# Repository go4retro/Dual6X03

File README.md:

# Dual 6X03 Adapter Schematic and Printed Circuit Board v1.0
This PCB will allow the use of two different 6X03 variants in a 6803-based system.  Only one CPU can be active at any time, and the CPU must be selected before boot.

## Theory
The 6X03 device can operate in modes 6801 configuration mode 2 or 3 only.  Essentially, Expanded Multiplexed mode with or without ROM.  At this moment, it is unclear how many of the 6X03 pins are tristated during RESET, so I took the safe approach of placing all known output lines (Address, Data, AS, E, R/W), and a few lines known to be outputs on the TANDY MC-10 (the first target of this PCB) to ensure operation.  If testing proves all lines to be in tristate or read state during RESET, I will simplify the schematic.

## License
Copyright (C) 2018  Jim Brain, RETRO Innovations

These files are free designs; you can redistribute them and/or modify
them under the terms of the Creative Commons Attribution-ShareAlike 
4.0 International License.

You should have received a copy of the license along with this
work. If not, see <http://creativecommons.org/licenses/by-sa/4.0/>.

These files are distributed in the hope that they will be useful,
but WITHOUT ANY WARRANTY; without even the implied warranty of
MERCHANTABILITY or FITNESS FOR A PARTICULAR PURPOSE.  See the
license for more details.

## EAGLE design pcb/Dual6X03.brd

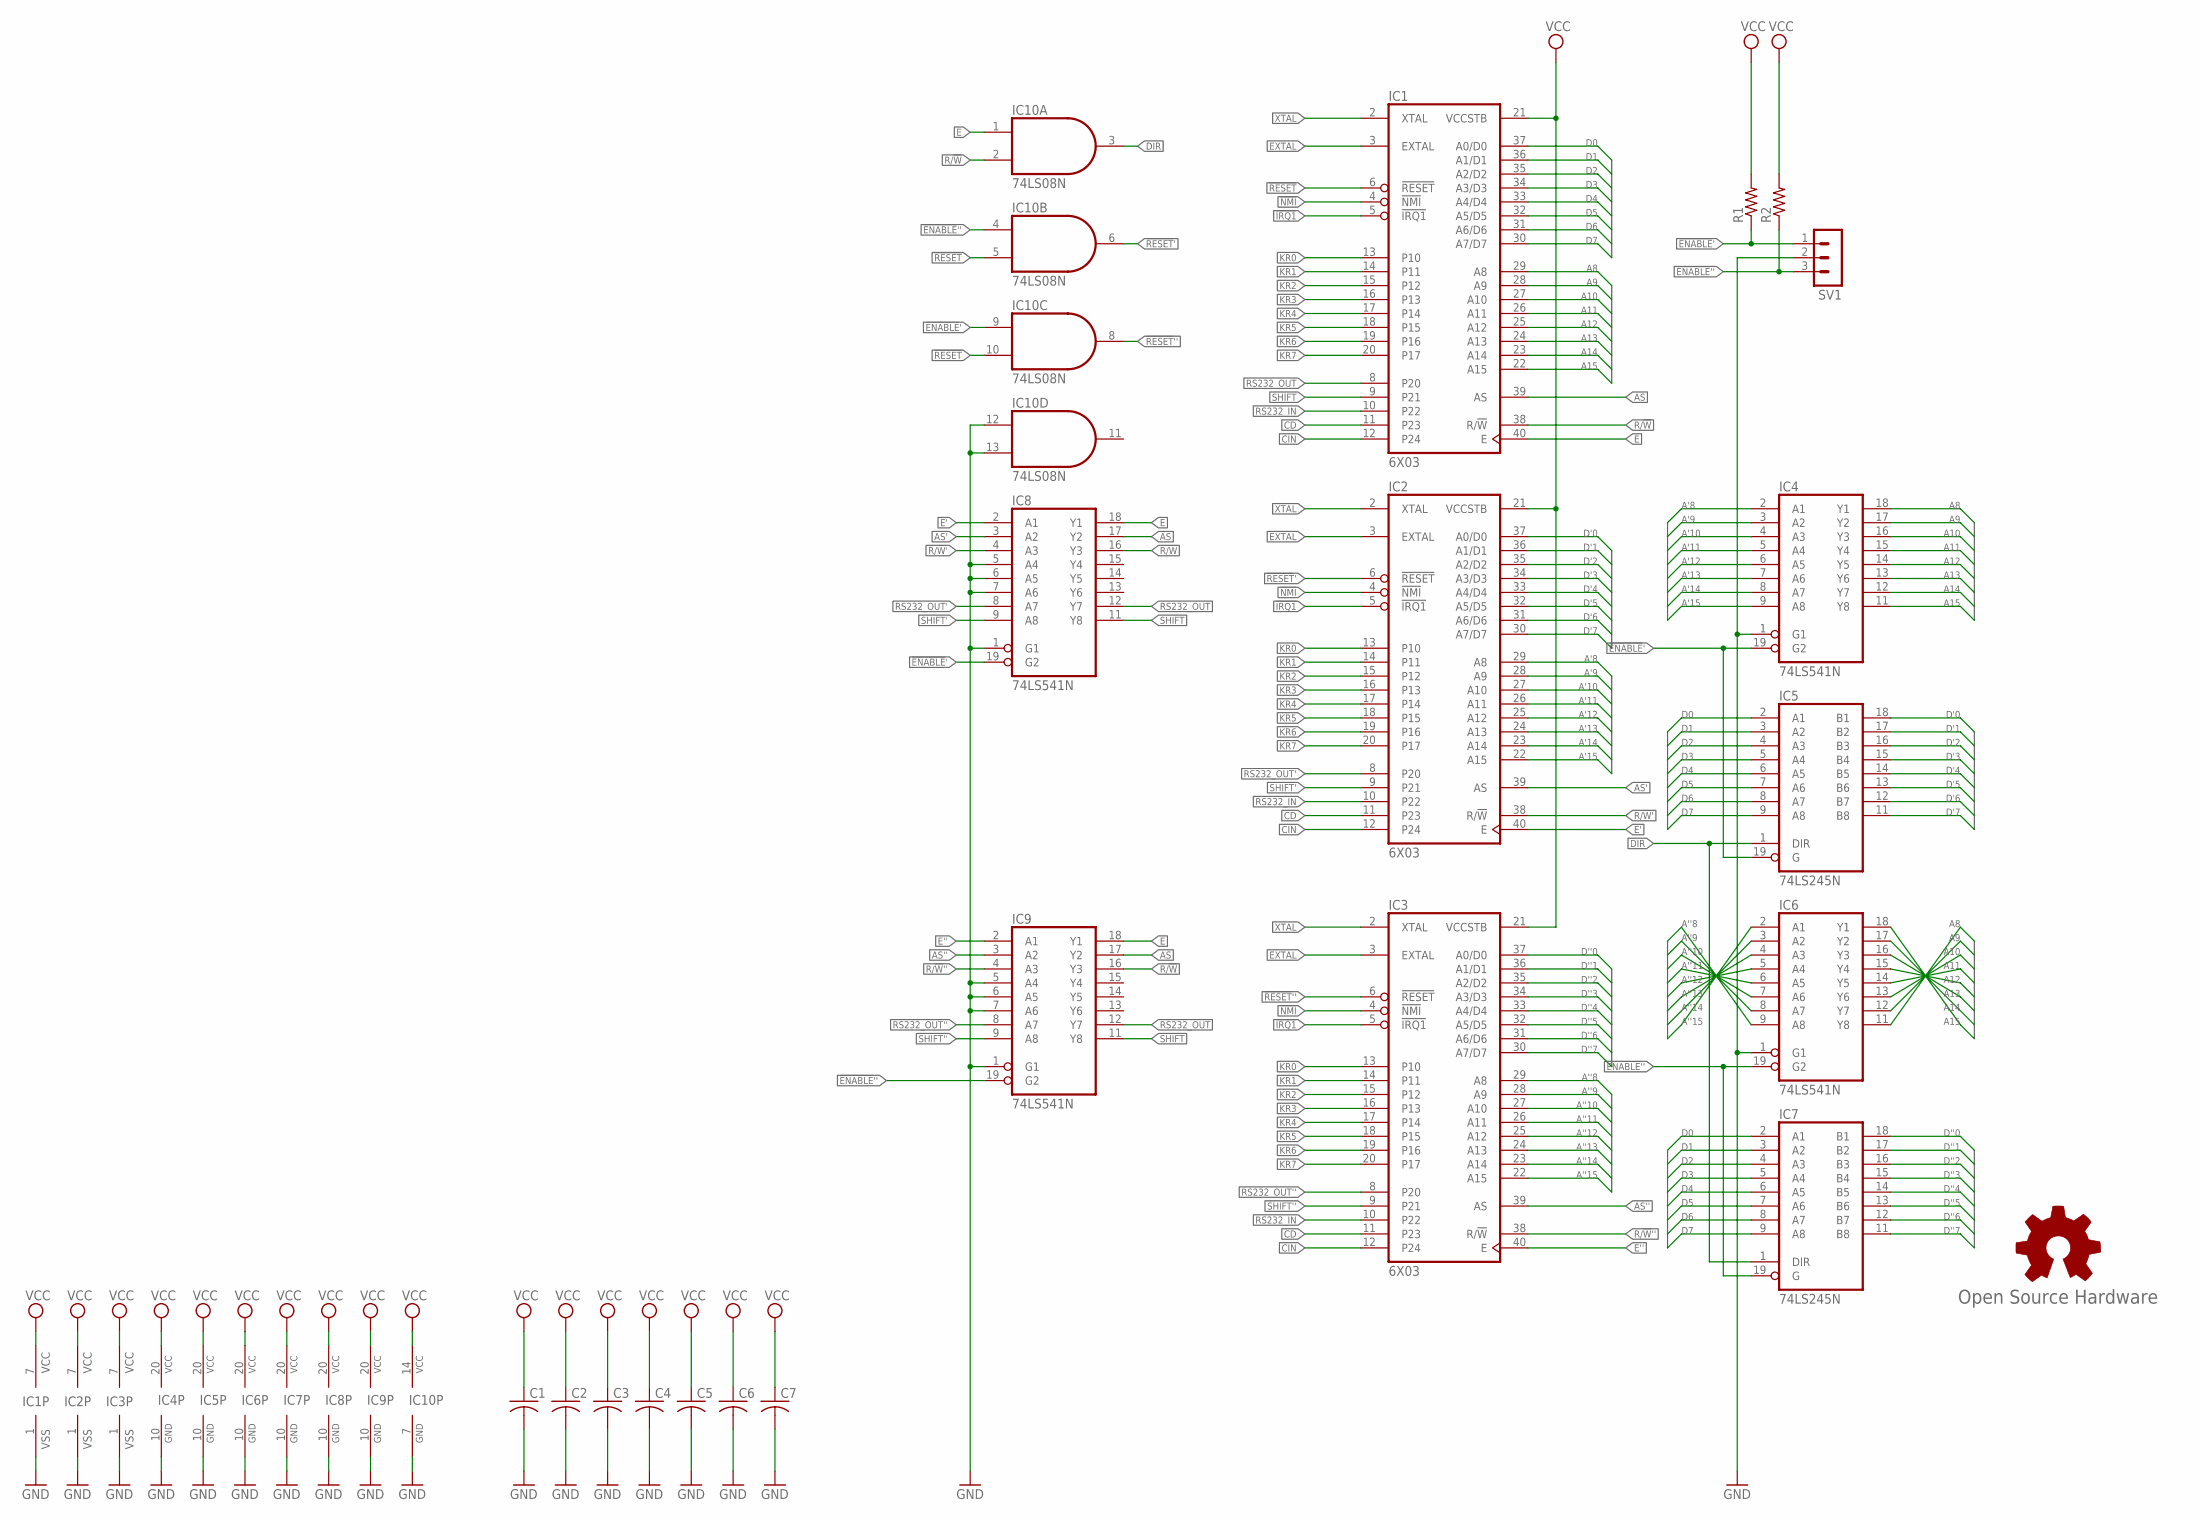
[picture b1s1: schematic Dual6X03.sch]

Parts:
C1, C2, C3, C4, C5, C6, C7: C-US025-025X050; C025-025X050
GOLD_ORB_SM1: Open Source Hardware; OSHW_8MM
IC1, IC2, IC3: 6X03; DIL40-ROUNDPAD
IC4, IC6, IC8, IC9: 74LS541N; DIL20
IC5, IC7: 74LS245N; DIL20
IC10: 74LS08N; DIL14
R1, R2: R-US_0204/2V; 0204V
SV1: MA03-1

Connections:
!ENABLE!': IC4.19 (G2), IC5.19 (G), IC8.19 (G2), IC10.9 (I0), R1.1, SV1.1
!ENABLE!'': IC6.19 (G2), IC7.19 (G), IC9.19 (G2), IC10.4 (I0), R2.1, SV1.3
!IRQ1: IC1.5 (!IRQ1), IC2.5 (!IRQ1), IC3.5 (!IRQ1)
!NMI: IC1.4 (!NMI), IC2.4 (!NMI), IC3.4 (!NMI)
!RESET: IC1.6 (!RESET), IC10.5 (I1), IC10.10 (I1)
!RESET!': IC2.6 (!RESET), IC10.6 (O)
!RESET!'': IC3.6 (!RESET), IC10.8 (O)
A8: IC1.29 (A8), IC4.18 (Y1), IC6.11 (Y8)
A9: IC1.28 (A9), IC4.17 (Y2), IC6.12 (Y7)
A10: IC1.27 (A10), IC4.16 (Y3), IC6.13 (Y6)
A11: IC1.26 (A11), IC4.15 (Y4), IC6.14 (Y5)
A12: IC1.25 (A12), IC4.14 (Y5), IC6.15 (Y4)
A13: IC1.24 (A13), IC4.13 (Y6), IC6.16 (Y3)
A14: IC1.23 (A14), IC4.12 (Y7), IC6.17 (Y2)
A15: IC1.22 (A15), IC4.11 (Y8), IC6.18 (Y1)
A'8: IC2.29 (A8), IC4.2 (A1)
A'9: IC2.28 (A9), IC4.3 (A2)
A'10: IC2.27 (A10), IC4.4 (A3)
A'11: IC2.26 (A11), IC4.5 (A4)
A'12: IC2.25 (A12), IC4.6 (A5)
A'13: IC2.24 (A13), IC4.7 (A6)
A'14: IC2.23 (A14), IC4.8 (A7)
A'15: IC2.22 (A15), IC4.9 (A8)
A''8: IC3.29 (A8), IC6.9 (A8)
A''9: IC3.28 (A9), IC6.8 (A7)
A''10: IC3.27 (A10), IC6.7 (A6)
A''11: IC3.26 (A11), IC6.6 (A5)
A''12: IC3.25 (A12), IC6.5 (A4)
A''13: IC3.24 (A13), IC6.4 (A3)
A''14: IC3.23 (A14), IC6.3 (A2)
A''15: IC3.22 (A15), IC6.2 (A1)
AS: IC1.39 (AS), IC8.17 (Y2), IC9.17 (Y2)
AS': IC2.39 (AS), IC8.3 (A2)
AS'': IC3.39 (AS), IC9.3 (A2)
CD: IC1.11 (P23), IC2.11 (P23), IC3.11 (P23)
CIN: IC1.12 (P24), IC2.12 (P24), IC3.12 (P24)
D0: IC1.37 (A0/D0), IC5.2 (A1), IC7.2 (A1)
D1: IC1.36 (A1/D1), IC5.3 (A2), IC7.3 (A2)
D2: IC1.35 (A2/D2), IC5.4 (A3), IC7.4 (A3)
D3: IC1.34 (A3/D3), IC5.5 (A4), IC7.5 (A4)
D4: IC1.33 (A4/D4), IC5.6 (A5), IC7.6 (A5)
D5: IC1.32 (A5/D5), IC5.7 (A6), IC7.7 (A6)
D6: IC1.31 (A6/D6), IC5.8 (A7), IC7.8 (A7)
D7: IC1.30 (A7/D7), IC5.9 (A8), IC7.9 (A8)
D'0: IC2.37 (A0/D0), IC5.18 (B1)
D'1: IC2.36 (A1/D1), IC5.17 (B2)
D'2: IC2.35 (A2/D2), IC5.16 (B3)
D'3: IC2.34 (A3/D3), IC5.15 (B4)
D'4: IC2.33 (A4/D4), IC5.14 (B5)
D'5: IC2.32 (A5/D5), IC5.13 (B6)
D'6: IC2.31 (A6/D6), IC5.12 (B7)
D'7: IC2.30 (A7/D7), IC5.11 (B8)
D''0: IC3.37 (A0/D0), IC7.18 (B1)
D''1: IC3.36 (A1/D1), IC7.17 (B2)
D''2: IC3.35 (A2/D2), IC7.16 (B3)
D''3: IC3.34 (A3/D3), IC7.15 (B4)
D''4: IC3.33 (A4/D4), IC7.14 (B5)
D''5: IC3.32 (A5/D5), IC7.13 (B6)
D''6: IC3.31 (A6/D6), IC7.12 (B7)
D''7: IC3.30 (A7/D7), IC7.11 (B8)
DIR: IC5.1 (DIR), IC7.1 (DIR), IC10.3 (O)
E: IC1.40 (E), IC8.18 (Y1), IC9.18 (Y1), IC10.1 (I0)
E': IC2.40 (E), IC8.2 (A1)
E'': IC3.40 (E), IC9.2 (A1)
EXTAL: IC1.3 (EXTAL), IC2.3 (EXTAL), IC3.3 (EXTAL)
GND: C1.2, C2.2, C3.2, C4.2, C5.2, C6.2, C7.2, IC1.1 (VSS), IC2.1 (VSS), IC3.1 (VSS), IC4.1 (G1), IC4.10 (GND), IC5.10 (GND), IC6.1 (G1), IC6.10 (GND), IC7.10 (GND), IC8.1 (G1), IC8.5 (A4), IC8.6 (A5), IC8.7 (A6), IC8.10 (GND), IC9.1 (G1), IC9.5 (A4), IC9.6 (A5), IC9.7 (A6), IC9.10 (GND), IC10.7 (GND), IC10.12 (I0), IC10.13 (I1), SV1.2
KR0: IC1.13 (P10), IC2.13 (P10), IC3.13 (P10)
KR1: IC1.14 (P11), IC2.14 (P11), IC3.14 (P11)
KR2: IC1.15 (P12), IC2.15 (P12), IC3.15 (P12)
KR3: IC1.16 (P13), IC2.16 (P13), IC3.16 (P13)
KR4: IC1.17 (P14), IC2.17 (P14), IC3.17 (P14)
KR5: IC1.18 (P15), IC2.18 (P15), IC3.18 (P15)
KR6: IC1.19 (P16), IC2.19 (P16), IC3.19 (P16)
KR7: IC1.20 (P17), IC2.20 (P17), IC3.20 (P17)
R/!W: IC1.38 (R/!W), IC8.16 (Y3), IC9.16 (Y3), IC10.2 (I1)
R/!W!': IC2.38 (R/!W), IC8.4 (A3)
R/!W!'': IC3.38 (R/!W), IC9.4 (A3)
RS232_IN: IC1.10 (P22), IC2.10 (P22), IC3.10 (P22)
RS232_OUT: IC1.8 (P20), IC8.12 (Y7), IC9.12 (Y7)
RS232_OUT': IC2.8 (P20), IC8.8 (A7)
RS232_OUT'': IC3.8 (P20), IC9.8 (A7)
SHIFT: IC1.9 (P21), IC8.11 (Y8), IC9.11 (Y8)
SHIFT': IC2.9 (P21), IC8.9 (A8)
SHIFT'': IC3.9 (P21), IC9.9 (A8)
VCC: C1.1, C2.1, C3.1, C4.1, C5.1, C6.1, C7.1, IC1.7 (VCC), IC1.21 (VCCSTB), IC2.7 (VCC), IC2.21 (VCCSTB), IC3.7 (VCC), IC3.21 (VCCSTB), IC4.20 (VCC), IC5.20 (VCC), IC6.20 (VCC), IC7.20 (VCC), IC8.20 (VCC), IC9.20 (VCC), IC10.14 (VCC), R1.2, R2.2
XTAL: IC1.2 (XTAL), IC2.2 (XTAL), IC3.2 (XTAL)

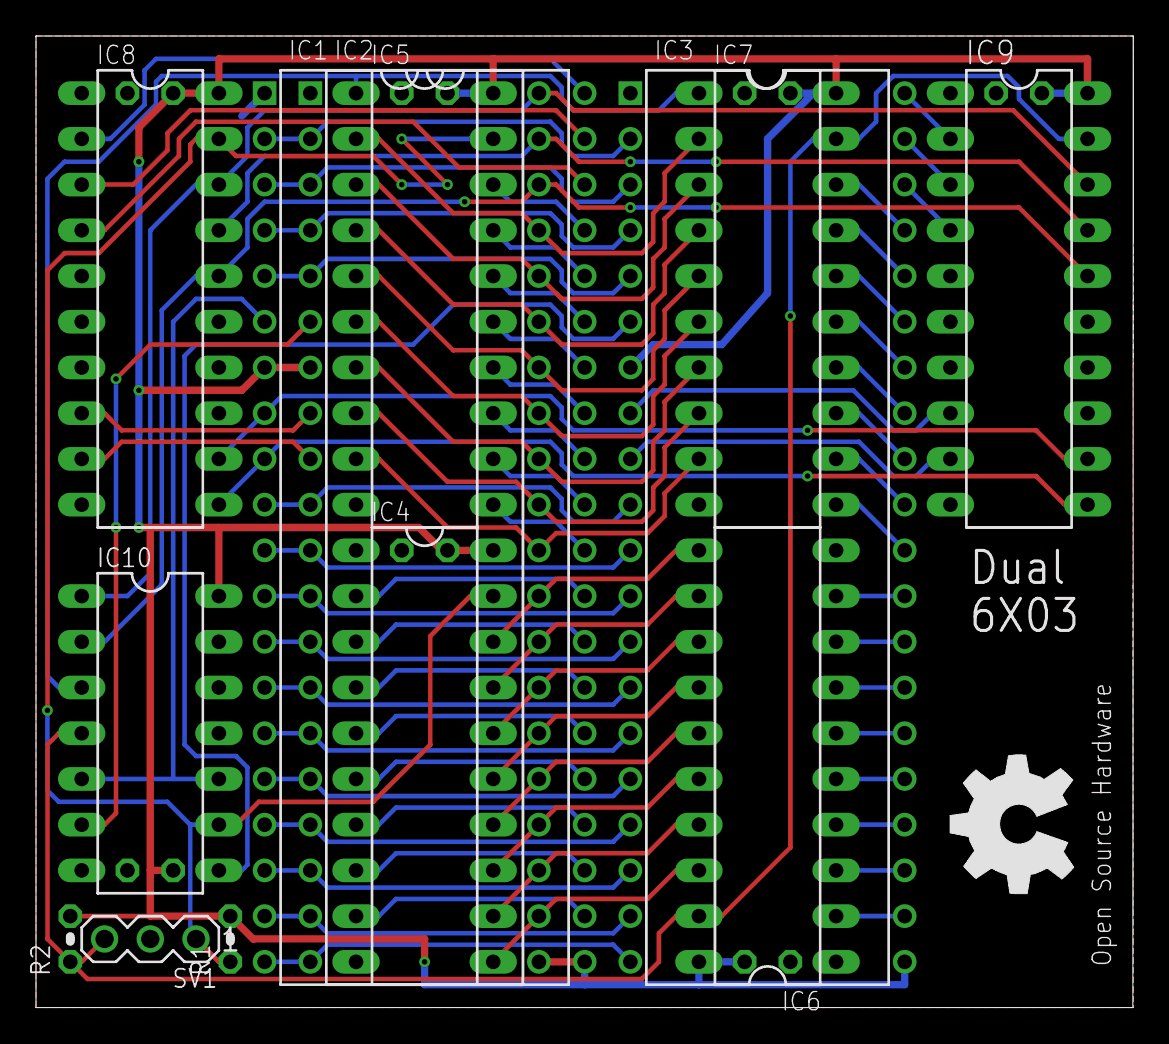
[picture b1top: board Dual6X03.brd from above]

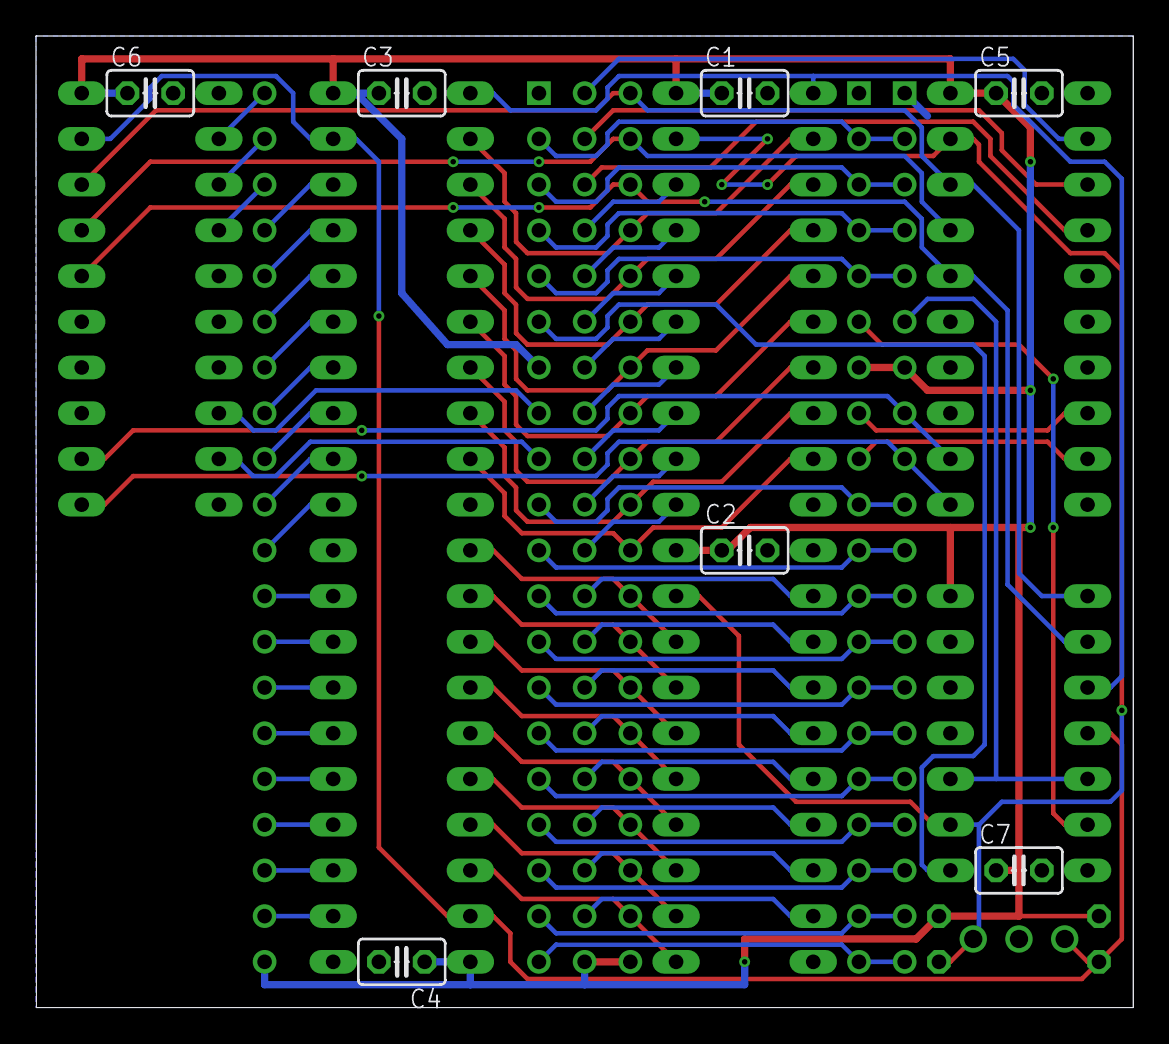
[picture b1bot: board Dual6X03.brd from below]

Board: 2 copper layers, 61.0 x 54.0 mm, 21 parts (7 on the bottom side), 86 nets.
